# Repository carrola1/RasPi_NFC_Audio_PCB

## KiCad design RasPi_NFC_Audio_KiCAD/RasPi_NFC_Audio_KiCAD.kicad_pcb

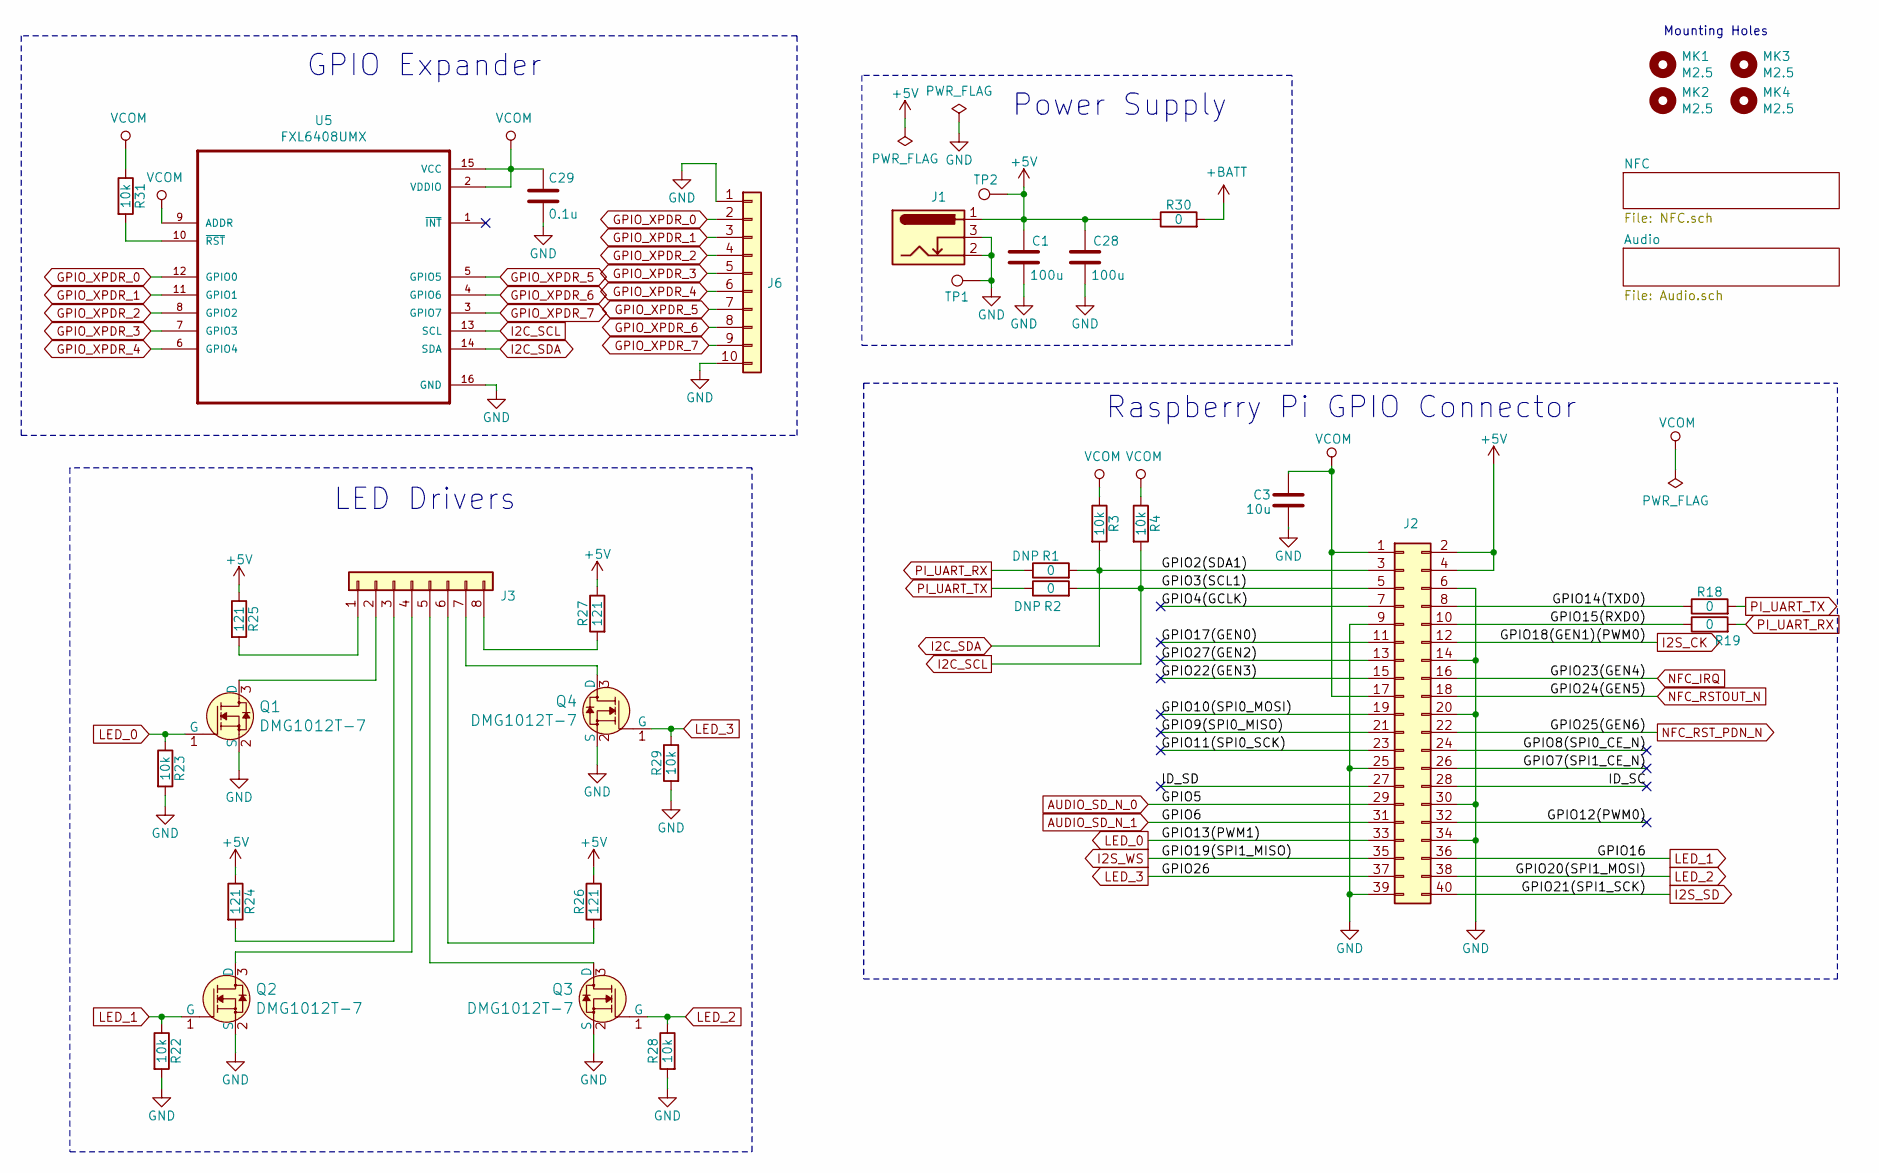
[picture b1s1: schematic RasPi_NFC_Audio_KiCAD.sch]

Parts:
C1, C28: 100u; C_1206_3216Metric_Pad1.42x1.75mm_HandSolder; Part # GRM31CD80J107ME39L; DigiKey 490-10525-1-ND
C3: 10u; C_0603_1608Metric_Pad1.05x0.95mm_HandSolder; Part # CL10A106MQ8NNNC; DigiKey 1276-1119-1-ND
C29: 0.1u; C_0603_1608Metric_Pad1.05x0.95mm_HandSolder; Part # CL10B104KB8NNNC; DigiKey 1276-1000-1-ND
J1: Barrel_Jack_Switch; BarrelJack_CUI_PJ-102AH_Horizontal; Part # PJ-102AH; DigiKey CP-102AH-ND
J2: Conn_02x20_Odd_Even; PinHeader_2x20_P2.54mm_Vertical; Part # M20-7831046; DigiKey 952-1837-ND
J3: Conn_01x08; PinHeader_1x08_P2.54mm_Horizontal; Part # M20-9960845; DigiKey 952-2249-ND
J6: Conn_01x10; PinHeader_1x10_P2.54mm_Horizontal; Part # 68016-210HLF; DigiKey 609-3322-ND
MK1, MK2, MK3, MK4: M2.5; MountingHole_2.7mm_M2.5
Q1, Q2, Q3, Q4: DMG1012T-7; SOT-523; MPN DMG1012T-7; Digi-Key_PN DMG1012T-7DICT-ND
R1, R2, R18, R19, R30: 0; R_0603_1608Metric_Pad1.05x0.95mm_HandSolder; Part # RC0603JR-070RL; DigiKey 311-0.0GRCT-ND
R3, R4, R22, R23, R28, R29, R31: 10k; R_0603_1608Metric_Pad1.05x0.95mm_HandSolder; Part # RNCP0603FTD10K0; DigiKey RNCP0603FTD10K0CT-ND
R24, R25, R26, R27: 121; R_0603_1608Metric_Pad1.05x0.95mm_HandSolder; Part # RMCF0603FT121R; DigiKey RMCF0603FT121RCT-ND
TP1, TP2: TestPoint; TestPoint_Keystone_5019_Minature
U5: FXL6408UMX; QFN40P260X180X55-16N; Part # FXL6408UMX; DigiKey FXL6408UMXCT-ND

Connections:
+5V: C1.1, C28.1, J1.1, J2.2, J2.4, R24.1, R25.1, R26.1, R27.1, R30.1, TP2.1; also elsewhere on the board
+BATT: R30.2; also elsewhere on the board
/GPIO4(GCLK): J2.7
/GPIO7(SPI1_CE_N): J2.26
/GPIO8(SPI0_CE_N): J2.24
/GPIO9(SPI0_MISO): J2.21
/GPIO10(SPI0_MOSI): J2.19
/GPIO11(SPI0_SCK): J2.23
/GPIO12(PWM0): J2.32
/GPIO14(TXD0): J2.8, R18.1
/GPIO15(RXD0): J2.10, R19.1
/GPIO17(GEN0): J2.11
/GPIO22(GEN3): J2.15
/GPIO27(GEN2): J2.13
/ID_SC: J2.28
/ID_SD: J2.27
AUDIO_SD_N_0: J2.29; also elsewhere on the board
AUDIO_SD_N_1: J2.31; also elsewhere on the board
GND: C1.2, C3.2, C28.2, C29.2, J1.2, J1.3, J2.6, J2.9, J2.14, J2.20, J2.25, J2.30, J2.34, J2.39, J6.1, J6.10, Q1.2 (S), Q2.2 (S), Q3.2 (S), Q4.2 (S), R22.2, R23.2, R28.2, R29.2, TP1.1, U5.16 (GND); also elsewhere on the board
GPIO_XPDR_0: J6.2, U5.12 (GPIO0)
GPIO_XPDR_1: J6.3, U5.11 (GPIO1)
GPIO_XPDR_2: J6.4, U5.8 (GPIO2)
GPIO_XPDR_3: J6.5, U5.7 (GPIO3)
GPIO_XPDR_4: J6.6, U5.6 (GPIO4)
GPIO_XPDR_5: J6.7, U5.5 (GPIO5)
GPIO_XPDR_6: J6.8, U5.4 (GPIO6)
GPIO_XPDR_7: J6.9, U5.3 (GPIO7)
I2C_SCL: J2.5, R2.2, R4.2, U5.13 (SCL)
I2C_SDA: J2.3, R1.2, R3.2, U5.14 (SDA)
I2S_CK: J2.12; also elsewhere on the board
I2S_SD: J2.40; also elsewhere on the board
I2S_WS: J2.35; also elsewhere on the board
LED_0: J2.33, Q1.1 (G), R23.1
LED_1: J2.36, Q2.1 (G), R22.1
LED_2: J2.38, Q3.1 (G), R28.1
LED_3: J2.37, Q4.1 (G), R29.1
NFC_IRQ: J2.16; also elsewhere on the board
NFC_RSTOUT_N: J2.18; also elsewhere on the board
NFC_RST_PDN_N: J2.22; also elsewhere on the board
unnamed: J3.1, R25.2
unnamed: J3.2, Q1.3 (D)
unnamed: J3.3, R24.2
unnamed: J3.4, Q2.3 (D)
unnamed: J3.5, Q3.3 (D)
unnamed: J3.6, R26.2
unnamed: J3.7, Q4.3 (D)
unnamed: J3.8, R27.2
unnamed: R31.2, U5.10 (~RST~)
PI_UART_RX: R1.1, R19.2; also elsewhere on the board
PI_UART_TX: R2.1, R18.2; also elsewhere on the board
VCOM: C3.1, C29.1, J2.1, J2.17, R3.1, R4.1, R31.1, U5.2 (VDDIO), U5.9 (ADDR), U5.15 (VCC); also elsewhere on the board

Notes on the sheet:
Mounting Holes
Power Supply
Raspberry Pi GPIO Connector
LED Drivers
GPIO Expander

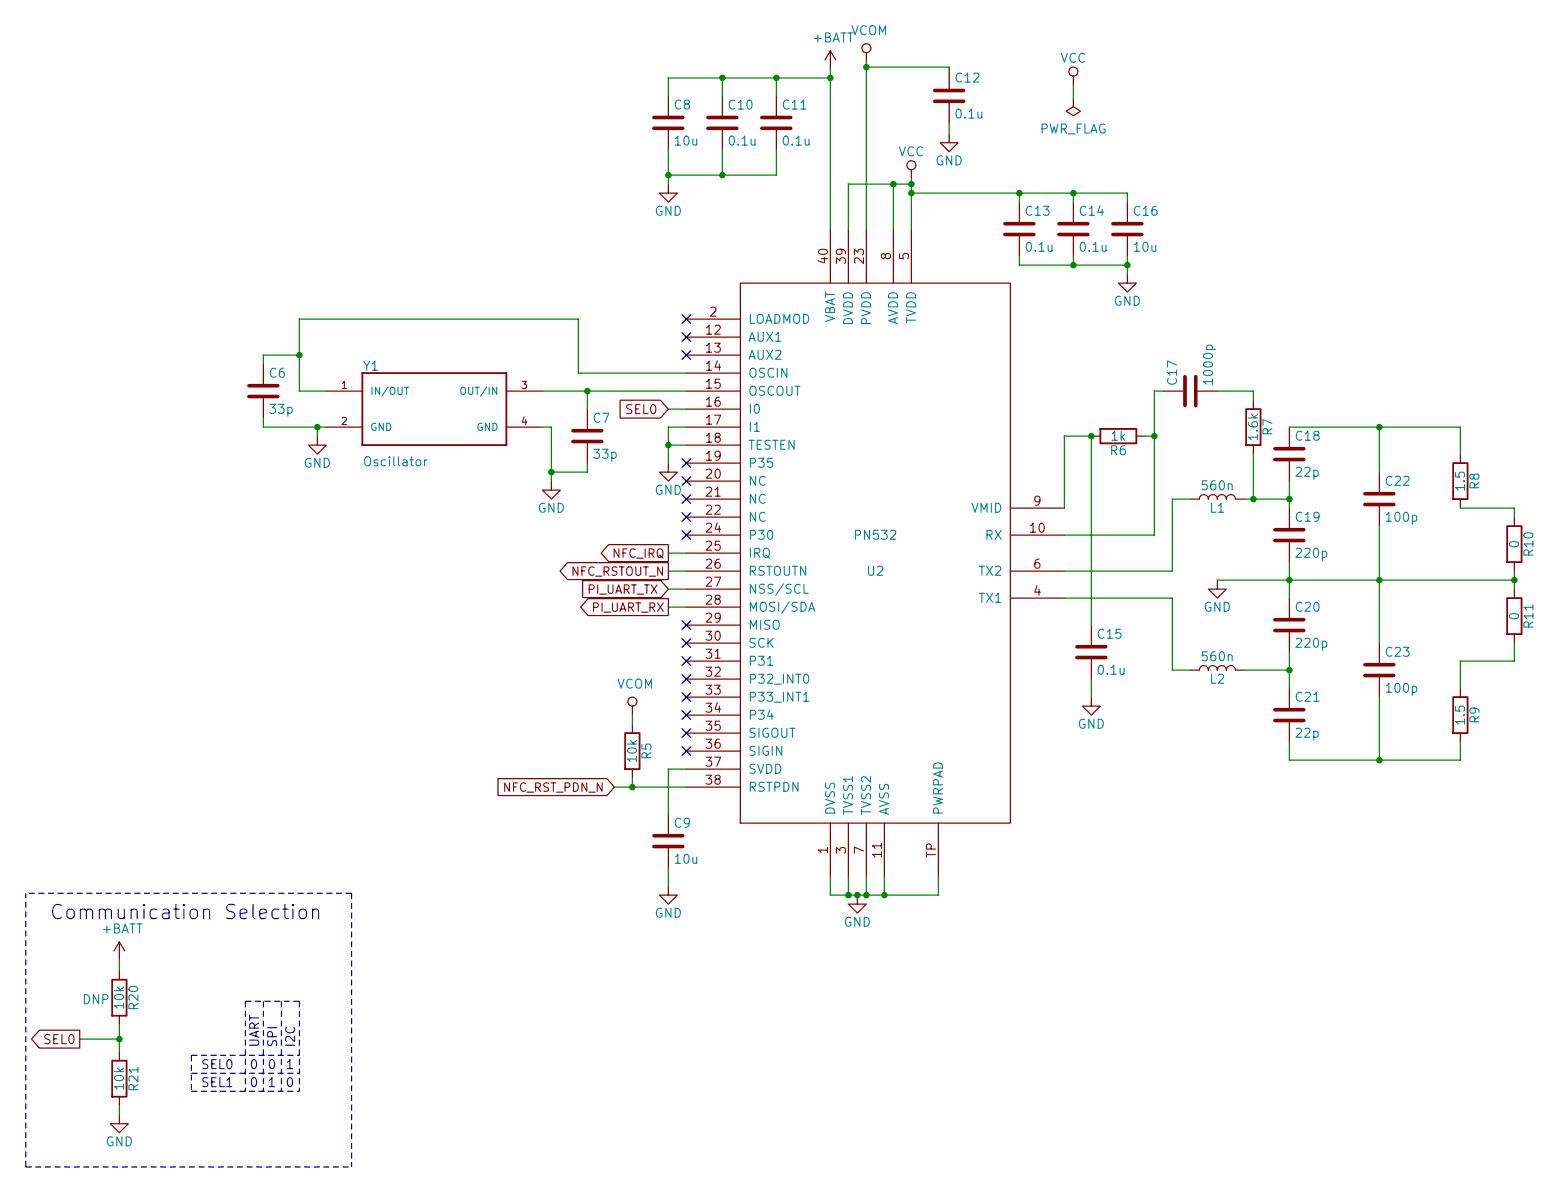
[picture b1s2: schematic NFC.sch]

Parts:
C6, C7: 33p; C_0603_1608Metric_Pad1.05x0.95mm_HandSolder; Part # C0603C330J1GACTU; DigiKey 399-7896-1-ND
C8, C9, C16: 10u; C_0603_1608Metric_Pad1.05x0.95mm_HandSolder; Part # CL10A106MQ8NNNC; DigiKey 1276-1119-1-ND
C10, C11, C12, C13, C14, C15: 0.1u; C_0603_1608Metric_Pad1.05x0.95mm_HandSolder; Part # CL10B104KB8NNNC; DigiKey 1276-1000-1-ND
C17: 1000p; C_0603_1608Metric_Pad1.05x0.95mm_HandSolder; Part # C0603C102J5RACTU; DigiKey 399-1083-1-ND
C18, C21: 22p; C_0603_1608Metric_Pad1.05x0.95mm_HandSolder; Part # C0603C220J1GACTU; DigiKey 399-7874-1-ND
C19, C20: 220p; C_0603_1608Metric_Pad1.05x0.95mm_HandSolder; Part # CC0603JRNPO9BN221; DigiKey 311-1073-1-ND
C22, C23: 100p; C_0603_1608Metric_Pad1.05x0.95mm_HandSolder; Part # CC0603JRNPO9BN101; DigiKey 311-1069-1-ND
L1, L2: 560n; L_0603_1608Metric_Pad1.05x0.95mm_HandSolder; Part # MLJ1608WR56JT000; DigiKey 445-174193-1-ND
R5, R20, R21: 10k; R_0603_1608Metric_Pad1.05x0.95mm_HandSolder; Part # RNCP0603FTD10K0; DigiKey RNCP0603FTD10K0CT-ND
R6: 1k; R_0603_1608Metric_Pad1.05x0.95mm_HandSolder; Part # RC0603JR-071KL; DigiKey 311-1.0KGRCT-ND
R7: 1.6k; R_0603_1608Metric_Pad1.05x0.95mm_HandSolder; Part # RC0603FR-071K6L; DigiKey 311-1.60KHRCT-ND
R8, R9: 1.5; R_0603_1608Metric_Pad1.05x0.95mm_HandSolder; Part # RMCF0603FT1R50; DigiKey RMCF0603FT1R50CT-ND
R10, R11: 0; R_0402_1005Metric; Part # RC1005J000CS; DigiKey 1276-3480-1-ND
U2: PN532; HVQFN40-6X6; Part # PN5321A3HN/C106,55; DigiKey 568-13228-ND
Y1: Oscillator; OSCCC500X320X105N; Part # 7M-27.120MAAJ-T; DigiKey 887-1424-1-ND

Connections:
+BATT: C8.1, C10.1, C11.1, R20.1, U2.40 (VBAT); also elsewhere on the board
GND: C6.2, C7.2, C8.2, C9.2, C10.2, C11.2, C12.2, C13.2, C14.2, C15.2, C16.2, C19.2, C20.1, C22.2, C23.1, R10.2, R11.1, R21.2, U2.1 (DVSS), U2.3 (TVSS1), U2.7 (TVSS2), U2.11 (AVSS), U2.17 (I1), U2.18 (TESTEN), U2.TP (PWRPAD), Y1.2 (GND), Y1.4 (GND); also elsewhere on the board
NFC_IRQ: U2.25 (IRQ); also elsewhere on the board
NFC_RSTOUT_N: U2.26 (RSTOUTN); also elsewhere on the board
NFC_RST_PDN_N: R5.2, U2.38 (RSTPDN); also elsewhere on the board
unnamed: C6.1, U2.14 (OSCIN), Y1.1 (IN/OUT)
unnamed: C7.1, U2.15 (OSCOUT), Y1.3 (OUT/IN)
unnamed: C9.1, U2.37 (SVDD)
unnamed: C15.1, R6.2, U2.9 (VMID)
unnamed: C17.1, R6.1, U2.10 (RX)
unnamed: C17.2, R7.1
unnamed: C18.1, C22.1, R8.1
unnamed: C18.2, C19.1, L1.2, R7.2
unnamed: C20.2, C21.1, L2.2
unnamed: C21.2, C23.2, R9.2
unnamed: L1.1, U2.6 (TX2)
unnamed: L2.1, U2.4 (TX1)
unnamed: R8.2, R10.1
unnamed: R9.1, R11.2
PI_UART_RX: U2.28 (MOSI/SDA); also elsewhere on the board
PI_UART_TX: U2.27 (NSS/SCL); also elsewhere on the board
SEL0: R20.2, R21.1, U2.16 (I0)
VCC: C13.1, C14.1, C16.1, U2.5 (TVDD), U2.8 (AVDD), U2.39 (DVDD)
VCOM: C12.1, R5.1, U2.23 (PVDD); also elsewhere on the board

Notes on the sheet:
SEL0
SEL1
UART
SPI
I2C
Communication Selection

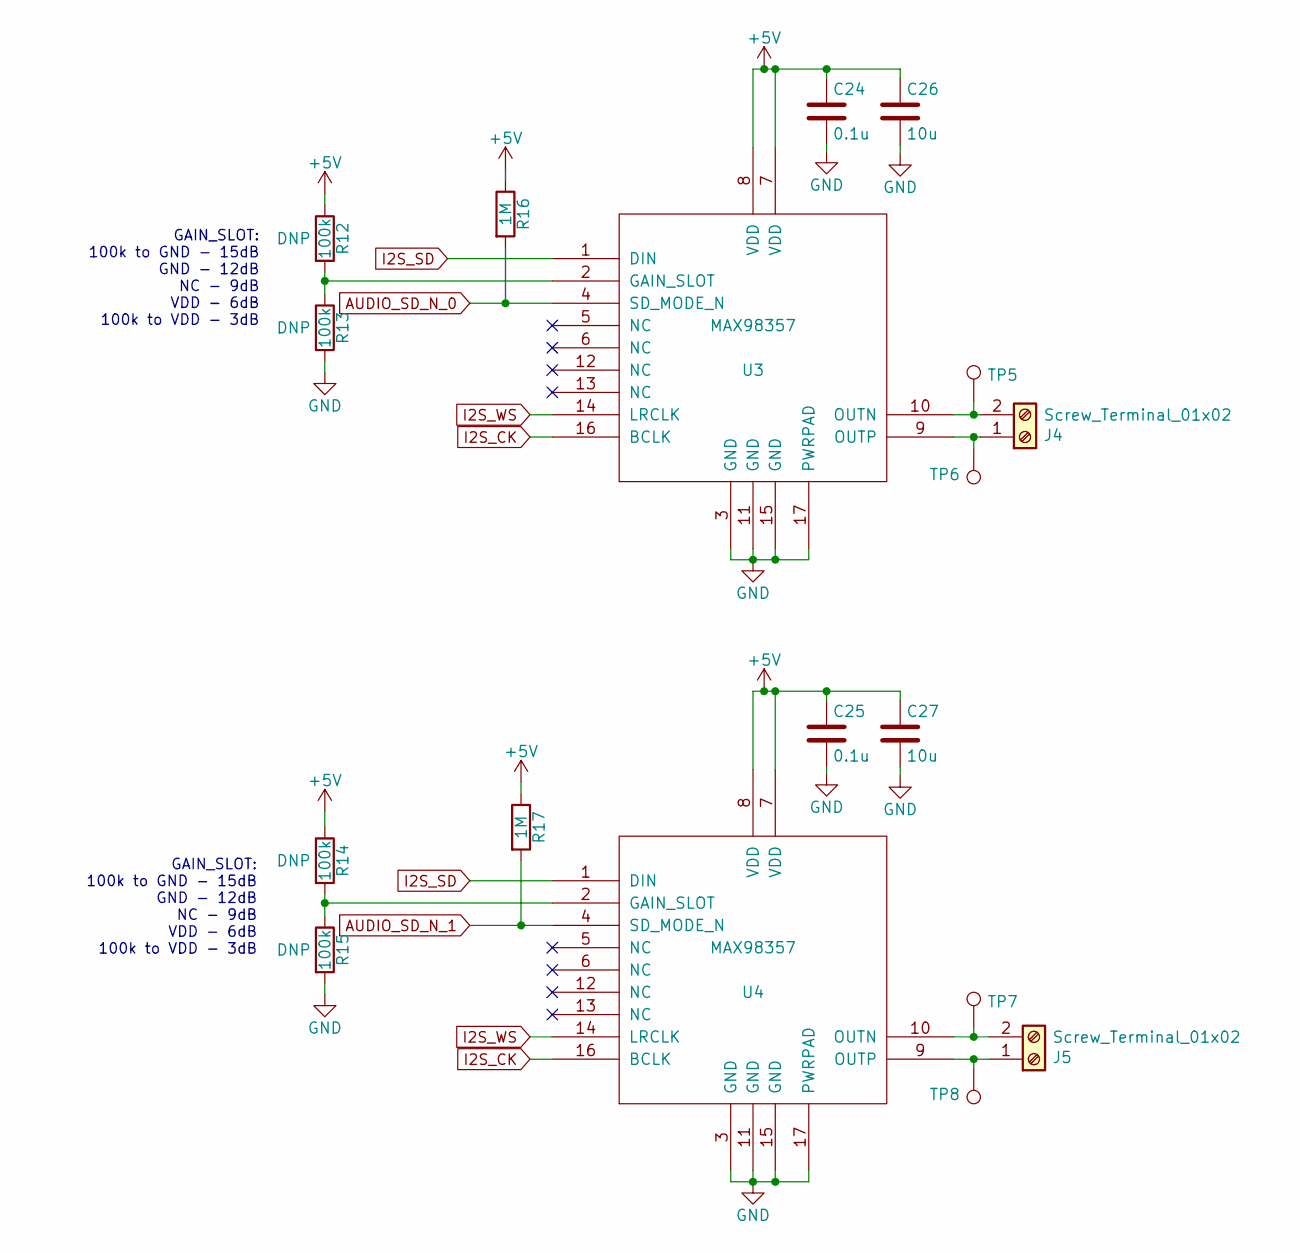
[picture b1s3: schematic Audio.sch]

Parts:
C24, C25: 0.1u; C_0603_1608Metric_Pad1.05x0.95mm_HandSolder; Part # CL10B104KB8NNNC; DigiKey 1276-1000-1-ND
C26, C27: 10u; C_0603_1608Metric_Pad1.05x0.95mm_HandSolder; Part # CL10A106MQ8NNNC; DigiKey 1276-1119-1-ND
J4, J5: Screw_Terminal_01x02; TerminalBlock_TE_282834-2_1x02_P2.54mm_Horizontal; Part # 282834-2; DigiKey A98333-ND
R12, R13, R14, R15: 100k; R_0603_1608Metric_Pad1.05x0.95mm_HandSolder; Part # RMCF0603FT100K; DigiKey RMCF0603FT100KCT-ND
R16, R17: 1M; R_0603_1608Metric_Pad1.05x0.95mm_HandSolder; Part # RC0603FR-071ML; DigiKey 311-1.00MHRCT-ND
TP5, TP6, TP7, TP8: TestPoint; TestPoint_Keystone_5019_Minature
U3, U4: MAX98357; QFN50P300X300X80-17N; Part # MAX98357AETE+T; DigiKey MAX98357AETE+TCT-ND

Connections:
+5V: C24.1, C25.1, C26.1, C27.1, R12.1, R14.1, R16.1, R17.1, U3.7 (VDD), U3.8 (VDD), U4.7 (VDD), U4.8 (VDD); also elsewhere on the board
AUDIO_SD_N_0: R16.2, U3.4 (SD_MODE_N); also elsewhere on the board
AUDIO_SD_N_1: R17.2, U4.4 (SD_MODE_N); also elsewhere on the board
GND: C24.2, C25.2, C26.2, C27.2, R13.2, R15.2, U3.3 (GND), U3.11 (GND), U3.15 (GND), U3.17 (PWRPAD), U4.3 (GND), U4.11 (GND), U4.15 (GND), U4.17 (PWRPAD); also elsewhere on the board
I2S_CK: U3.16 (BCLK), U4.16 (BCLK); also elsewhere on the board
I2S_SD: U3.1 (DIN), U4.1 (DIN); also elsewhere on the board
I2S_WS: U3.14 (LRCLK), U4.14 (LRCLK); also elsewhere on the board
unnamed: J4.1, TP6.1, U3.9 (OUTP)
unnamed: J4.2, TP5.1, U3.10 (OUTN)
unnamed: J5.1, TP8.1, U4.9 (OUTP)
unnamed: J5.2, TP7.1, U4.10 (OUTN)
unnamed: R12.2, R13.1, U3.2 (GAIN_SLOT)
unnamed: R14.2, R15.1, U4.2 (GAIN_SLOT)

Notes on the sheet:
GAIN_SLOT: 100k to GND - 15dB GND - 12dB NC - 9dB VDD - 6dB 100k to VDD - 3dB

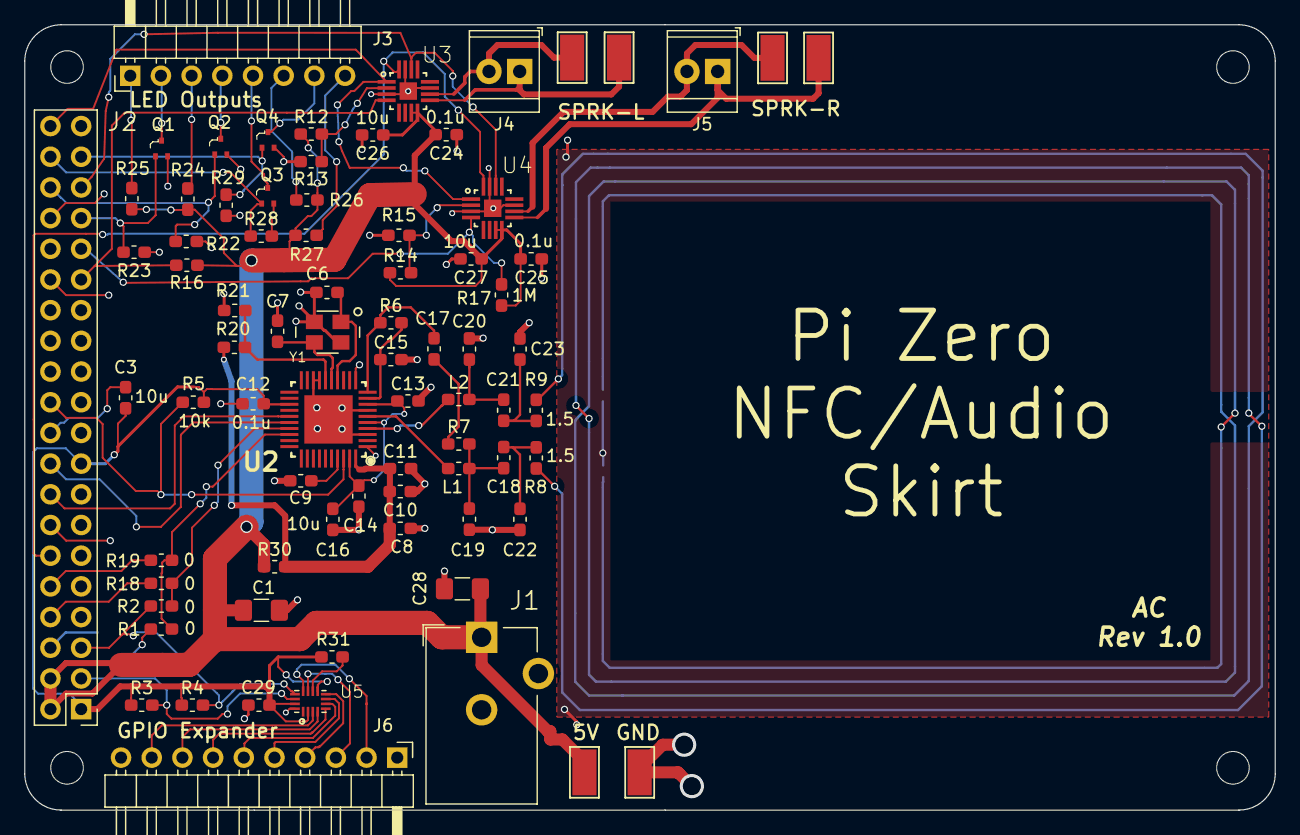
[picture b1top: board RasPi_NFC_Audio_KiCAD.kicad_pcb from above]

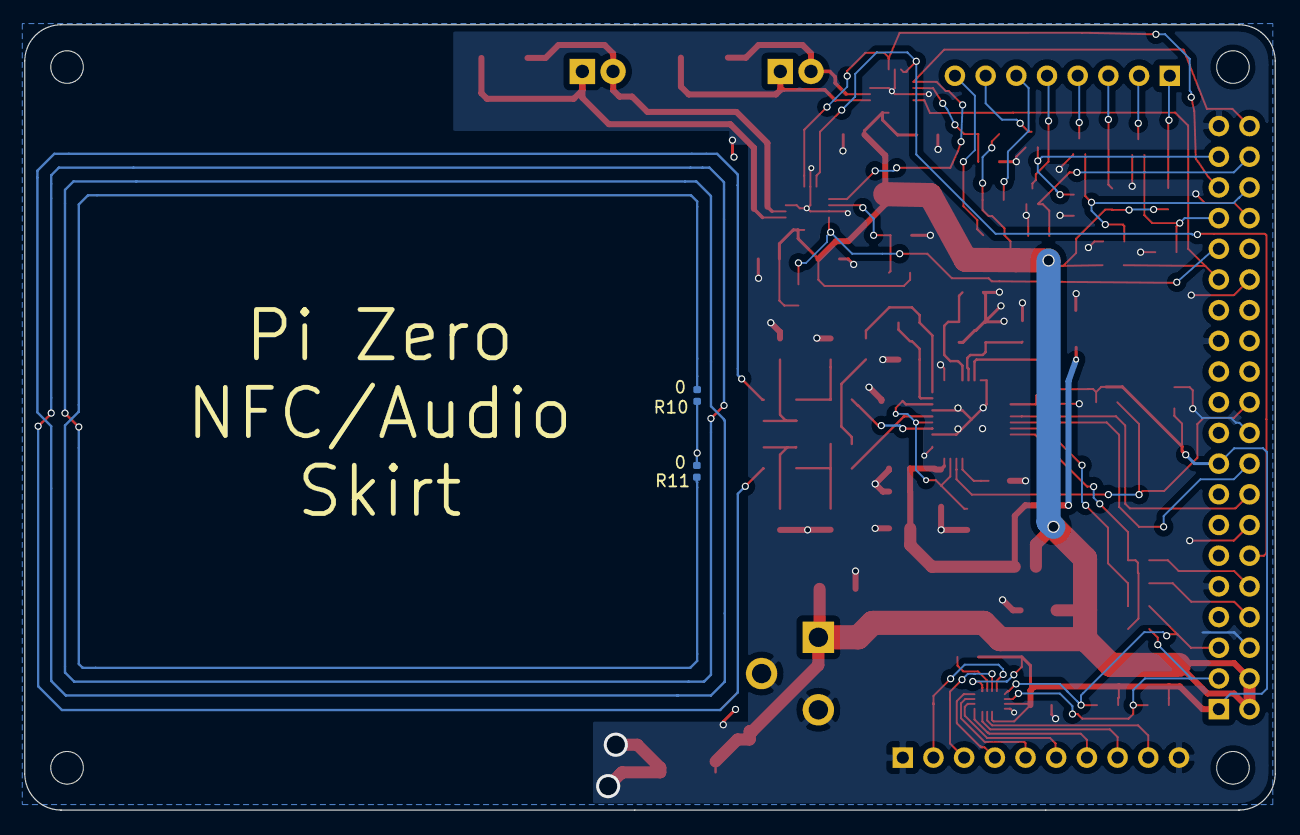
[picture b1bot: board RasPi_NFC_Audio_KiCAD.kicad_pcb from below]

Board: 2 copper layers, 103.5 x 65.0 mm, 84 parts (2 on the bottom side), 61 nets.

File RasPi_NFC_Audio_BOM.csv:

"Id";"Designator";"Package";"Quantity";"Designation";"Supplier and ref";
1;"J2";"PinSocket_2x20_P2.54mm_Vertical";1;"Conn_02x20_Odd_Even";;;
2;"R16,R17";"R_0603_HandSoldering";2;"1.5";;;
3;"R19,R18";"R_0402";2;"0";;;
4;"C1";"C_1206_3216Metric_Pad1.42x1.75mm_HandSolder";1;"100u";;;
5;"C2,C3,C4,C5,C8,C9,C16,C26,C27";"C_0603_1608Metric_Pad1.05x0.95mm_HandSolder";9;"10u";;;
6;"C6,C7";"C_0603_1608Metric_Pad1.05x0.95mm_HandSolder";2;"33p";;;
7;"C10,C11,C12,C13,C14,C15,C24,C25";"C_0603_1608Metric_Pad1.05x0.95mm_HandSolder";8;"0.1u";;;
8;"C17";"C_0603_1608Metric_Pad1.05x0.95mm_HandSolder";1;"1000p";;;
9;"C18,C21";"C_0603_1608Metric_Pad1.05x0.95mm_HandSolder";2;"22p";;;
10;"C19,C20";"C_0603_1608Metric_Pad1.05x0.95mm_HandSolder";2;"220p";;;
11;"C22,C23";"C_0603_1608Metric_Pad1.05x0.95mm_HandSolder";2;"100p";;;
12;"J1";"BarrelJack_CUI_PJ-102AH_Horizontal";1;"Barrel_Jack_Switch";;;
13;"J3";"PinHeader_1x10_P2.54mm_Vertical";1;"Connector_01x10";;;
14;"J4,J5";"TerminalBlock_TE_282834-2_1x02_P2.54mm_Horizontal";2;"Screw_Terminal_01x02";;;
15;"L1,L2";"L_0603_1608Metric_Pad1.05x0.95mm_HandSolder";2;"560n";;;
16;"R1,R2,R10,R11,R18,R19";"R_0603_1608Metric_Pad1.05x0.95mm_HandSolder";6;"0";;;
17;"R3,R4,R5,R20,R21,R22,R23";"R_0603_1608Metric_Pad1.05x0.95mm_HandSolder";7;"10k";;;
18;"R6";"R_0603_1608Metric_Pad1.05x0.95mm_HandSolder";1;"1k";;;
19;"R7";"R_0603_1608Metric_Pad1.05x0.95mm_HandSolder";1;"1.6k";;;
20;"R8,R9";"R_0603_1608Metric_Pad1.05x0.95mm_HandSolder";2;"1.5";;;
21;"R12,R13,R14,R15";"R_0603_1608Metric_Pad1.05x0.95mm_HandSolder";4;"100k";;;
22;"R16,R17";"R_0603_1608Metric_Pad1.05x0.95mm_HandSolder";2;"1M";;;
23;"TP3,TP4";"TestPoint_Pad_2.0x2.0mm";2;"TestPoint";;;
24;"U1";"SOT-23-5";1;"MIC5225-3.3V";;;
25;"U2";"HVQFN40-6X6";1;"PN532";;;
26;"U3,U4";"QFN50P300X300X80-17N";2;"MAX98357";;;
27;"Y1";"OSCCC500X320X105N";1;"Oscillator";;;
28;"TP1,TP2,TP5,TP6,TP7,TP8";"TestPoint_Keystone_5019_Minature";6;"TestPoint";;;
29;"MK1,MK2,MK3,MK4";"MountingHole_2.7mm_M2.5";4;"M2.5";;;

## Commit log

2020-01-11 Added protocol selection jumpers
2020-01-11 Schematic update
2020-01-12 Schematic Updates
2020-01-12 Schematic changes
2020-01-14 Startednfootprint assignment
2020-01-14 Layout started
2020-01-15 Layout updates
2020-01-17 Gerbers and BOM generated
2020-01-20 Added GPIO expander to schematic
2020-01-20 Updated layout for GPIO expander
2020-01-21 Updated BOM
2020-01-21 Gerbers generated
2020-02-10 Updated centroid files
2020-04-02 Adding PCBWay files
